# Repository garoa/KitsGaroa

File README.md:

KitsGaroa
=========

Kits físicos de eletrônica

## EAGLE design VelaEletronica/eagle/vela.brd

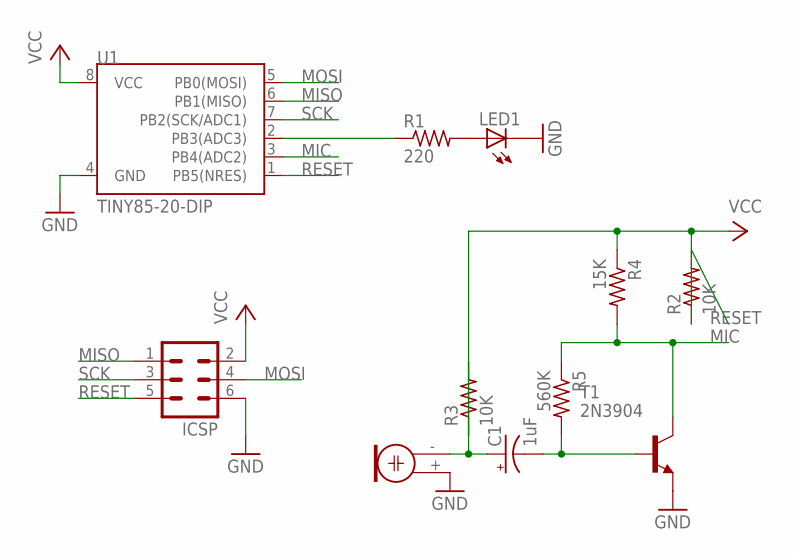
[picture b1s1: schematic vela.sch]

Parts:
C1: 1uF; E2-5
ICSP: MA03-2
LED1: LED5MM
M1: ELECTRET_MICROPHON-TOM-1545P-R; TOM-1545P-R
R1: 220; 0207/2V
R2, R3: 10K; 0207/2V
R4: 15K; 0207/2V
R5: 560K; 0207/2V
T1: 2N3904; TO92
U1: TINY85-20-DIP; DIP08

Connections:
GND: ICSP.6, LED1.K (C), M1.+ (1), T1.3 (E), U1.4 (GND)
MIC: R4.2, R5.1, T1.1 (C), U1.3 (PB4(ADC2))
MISO: ICSP.1, U1.6 (PB1(MISO))
MOSI: ICSP.4, U1.5 (PB0(MOSI))
unnamed: LED1.A, R1.2
unnamed: C1.+, M1.- (2), R3.2
unnamed: C1.-, R5.2, T1.2 (B)
unnamed: R1.1, U1.2 (PB3(ADC3))
RESET: ICSP.5, R2.2, U1.1 (PB5(NRES))
SCK: ICSP.3, U1.7 (PB2(SCK/ADC1))
VCC: ICSP.2, R2.1, R3.1, R4.1, U1.8 (VCC)

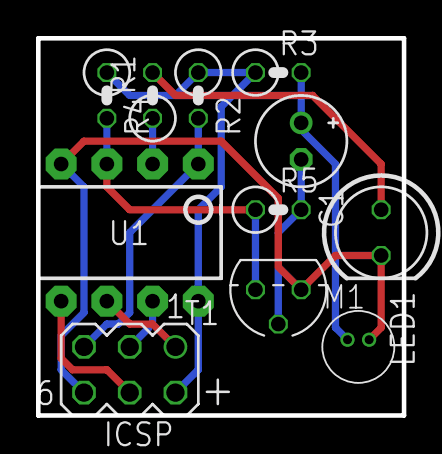
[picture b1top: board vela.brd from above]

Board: 2 copper layers, 20.3 x 21.0 mm, 11 parts (0 on the bottom side), 11 nets.

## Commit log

2014-12-10 ideias para kits
2014-12-10 Vela Eletrônica por DQ
2014-12-10 outra idéia de um kit que seria bacana fazer...
2014-12-10 consertando alguns problemas

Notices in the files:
parts and their libraries:
SparkFun-DigitalIC: Licensing: Creative Commons ShareAlike 4.0 International - https://creativecommons.org/licenses/by-sa/4.0
